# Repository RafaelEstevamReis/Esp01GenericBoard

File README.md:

# Esp01GenericBoard
ESP 01 - Generic board

* 5v DC IN
* 5v Serial
* Exposed GPIO0 and GPIO2 with 3v3 and GND connectors

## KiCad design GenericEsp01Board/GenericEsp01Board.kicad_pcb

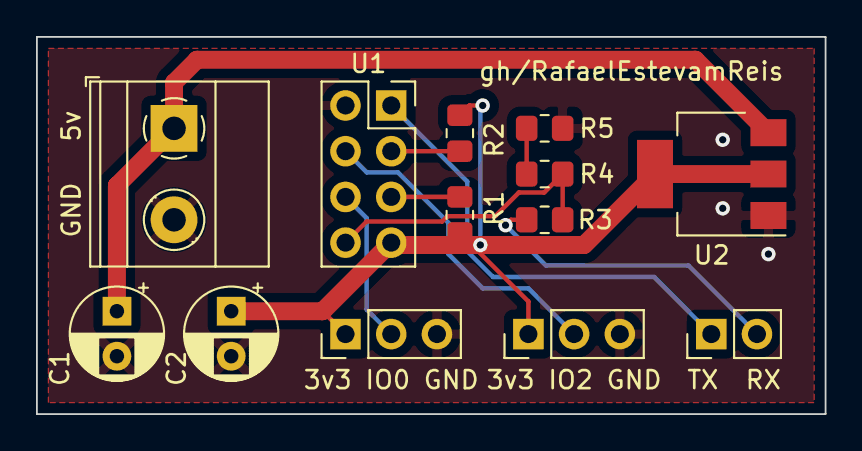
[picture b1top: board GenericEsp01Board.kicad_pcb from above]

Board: 2 copper layers, 43.8 x 21.0 mm, 13 parts (0 on the bottom side), 11 nets.

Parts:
3v3 IO0 GND: IO0; PinHeader_1x03_P2.54mm_Vertical
3v3 IO2 GND: IO2; PinHeader_1x03_P2.54mm_Vertical
C1: 100uf; CP_Radial_D5.0mm_P2.50mm
C2: 10uF; CP_Radial_D5.0mm_P2.50mm
GND   5v: DC IN; TerminalBlock_Phoenix_MKDS-1,5-2-5.08_1x02_P5.08mm_Horizont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
R1, R2: 10k; R_0805_2012Metric_Pad1.20x1.40mm_HandSolder
R3, R4, R5: 1k; R_0805_2012Metric_Pad1.20x1.40mm_HandSolder
TX  RX: 5vSerial; PinHeader_1x02_P2.54mm_Vertical
U1: ESP; PinSocket_2x04_P2.54mm_Vertical
U2: AMS1117; SOT-223-3_TabPin2

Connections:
/3v3: 3v3 IO0 GND.1, 3v3 IO2 GND.1, C2.1, R1.2, R2.2, U1.7, U2.2
/3v3_RX: R3.1, R4.2, U1.8
/3v3_TX: TX RX.1, U1.1
/DC_IN: C1.1, GND 5v.1, U2.3
/GPIO0: 3v3 IO0 GND.2, U1.6
/GPIO2: 3v3 IO2 GND.2, U1.4
GND: 3v3 IO0 GND.3, 3v3 IO2 GND.3, C1.2, C2.2, GND 5v.2, R5.1, U1.2, U2.1
unnamed: R3.2, TX RX.2
unnamed: R1.1, U1.5
unnamed: R2.1, U1.3
unnamed: R4.1, R5.2

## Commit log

2022-04-08 First
2022-04-09 Add THT
